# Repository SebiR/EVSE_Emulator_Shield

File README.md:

# EVSE Emulator Arduino Shield
An Arduino shield to emulate an EVSE (Electric Vehicle Supply Equipment), so basically it emulates a car charger

## Features
* on-board charge pump and inverter for +12/-12V pilot signal
* Pilot level and PP level go to ADC channels
* Status LEDs

## Firmware
The Firmware is still in progress. It will be documented once finished

### Known Issues
* ADC values are dependent from USB voltage

## Resources
https://www.goingelectric.de/wiki/Typ2-Signalisierung-und-Steckercodierung/

## Disclaimer
This project was created to test an EV emulator. This project is not intended to be used in an actual Wallbox. 
There are no safety features and neither the firmware nor the hardware are created with robustness and safety in mind.
Although the state machine would be able to work as a full EVSE.

Use at your own risk. Im not liable for burning houses, cars or pants.

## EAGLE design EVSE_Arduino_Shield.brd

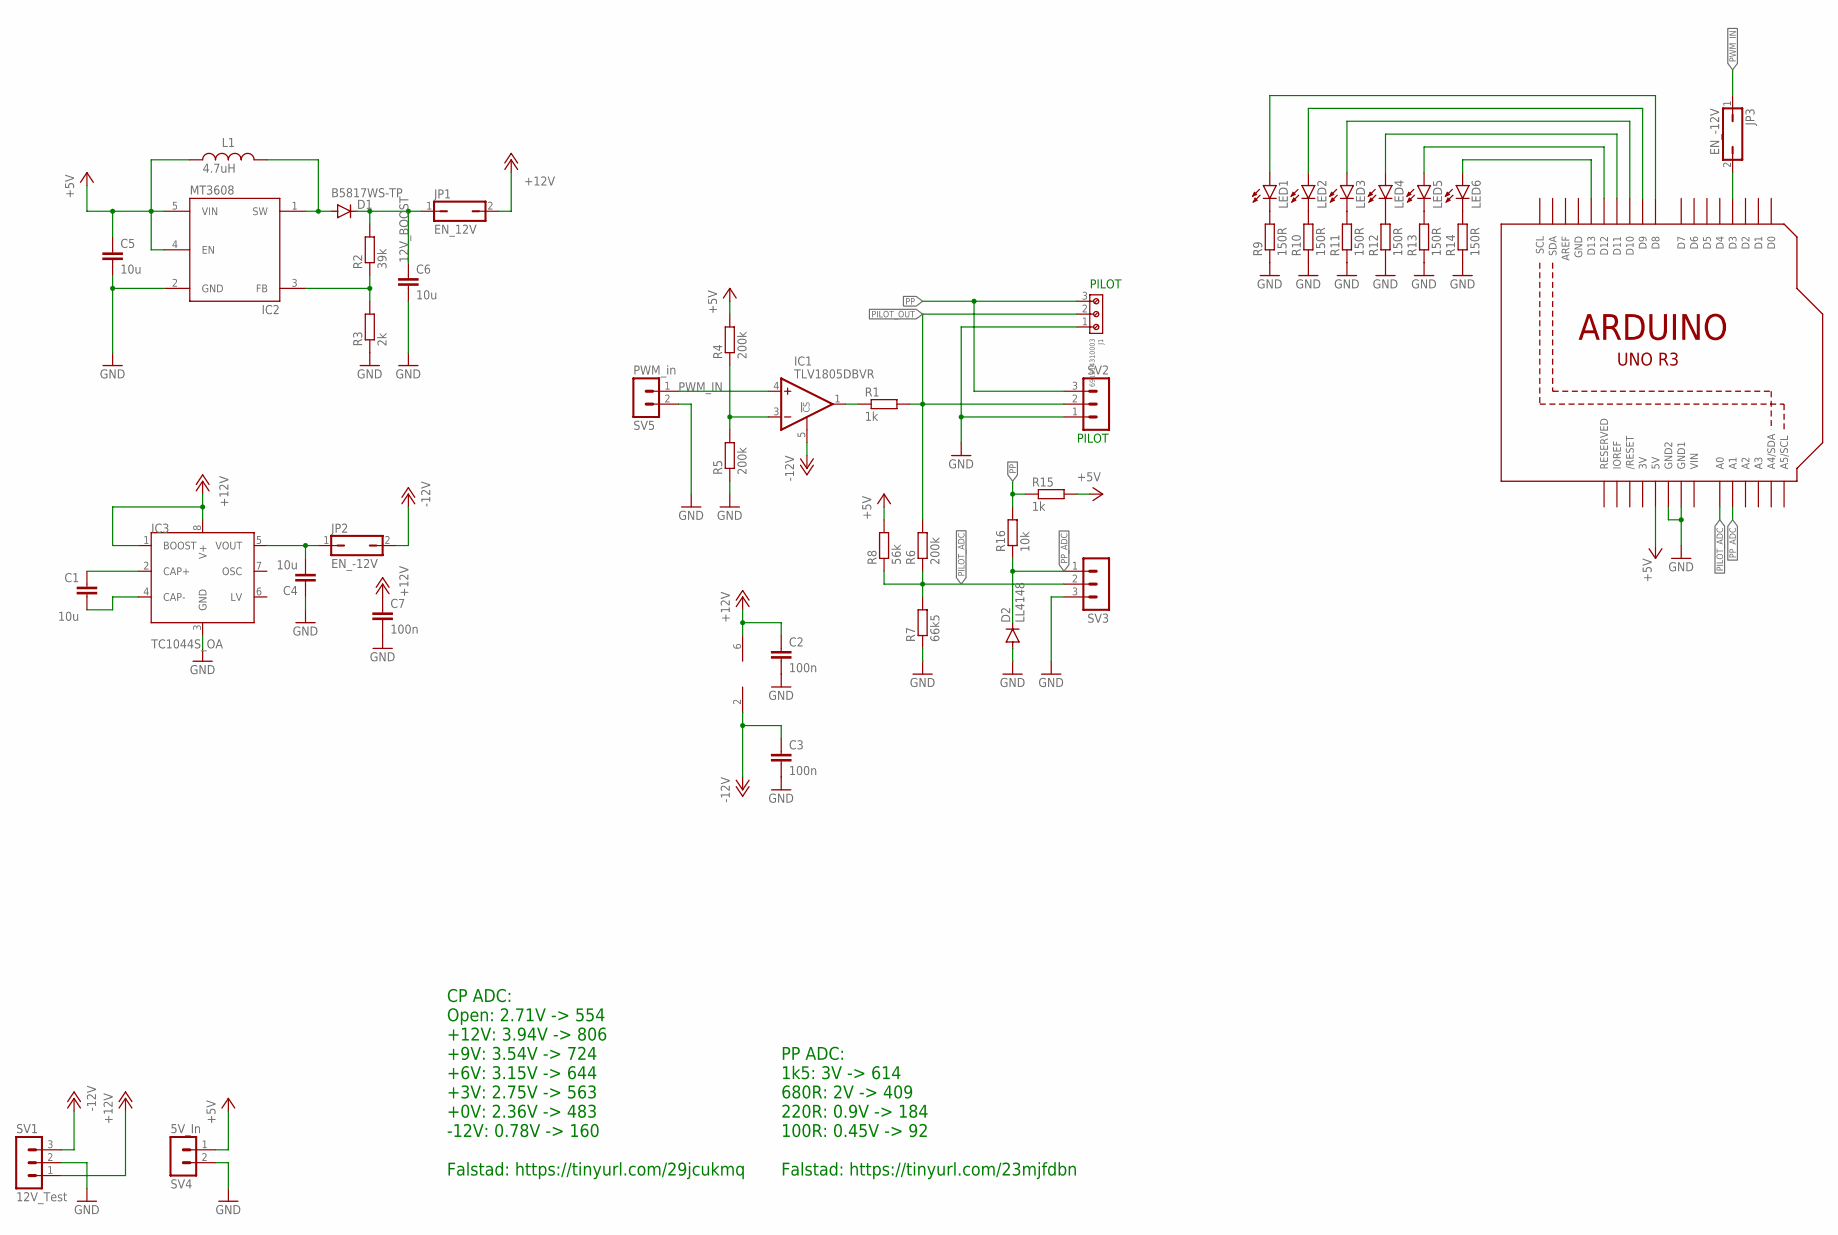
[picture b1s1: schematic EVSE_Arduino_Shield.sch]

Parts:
C1, C4, C5, C6: 10u; C0805
C2, C3, C7: 100n; C0603
D1: B5817WS-TP; SOD323-R
D2: LL4148; SOD80C
IC1: TLV1805DBVR; SOT23-6
IC2: MT3608; SOT23-6
IC3: TC1044S_OA; SO08
J1: 691214310003
JP1: EN_12V; JP1
JP2, JP3: EN_-12V; JP1
L1: 4.7uH; WE-PMI_0805_H1
LED1, LED2, LED3, LED4, LED5, LED6: LEDCHIP-LED0603; CHIP-LED0603
R1: 1k; R0805
R2: 39k; R0603
R3: 2k; R0603
R4, R5, R6: 200k; R0603
R7: 66k5; R0603
R8: 56k; R0603
R9, R10, R11, R12, R13, R14: 150R; R0603
R15: 1k; R0603
R16: 10k; R0603
SV1: 12V_Test; MA03-1
SV2, SV3: MA03-1
SV4: 5V_In; MA02-1
SV5: PWM_in; MA02-1
U2: ARDUINOR3-DIMENSION; ARDUINOR3

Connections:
3V: U2.3V
12V_BOOST: C6.1, D1.C, JP1.1, R2.2
+5V: C5.1, IC2.4 (EN), IC2.5 (VIN), L1.1, R4.2, R8.2, R15.2, SV4.1, U2.5V
+12V: C2.1, C7.1, IC1.6 (V+), IC3.1 (BOOST), IC3.8 (V+), JP1.2, SV1.1
-12V: C3.1, IC1.2 (V-), IC1.5 (!CS), JP2.2, SV1.3
BOOST_SW: D1.A, IC2.1 (SW), L1.2
GND: C2.2, C3.2, C4.1, C5.2, C6.2, C7.2, D2.A, IC2.2 (GND), IC3.3 (GND), J1.1, R3.1, R5.1, R7.1, R9.1, R10.1, R11.1, R12.1, R13.1, R14.1, SV1.2, SV2.1, SV3.3, SV4.2, SV5.2, U2.GND, U2.GND1, U2.GND2
unnamed: LED1.C, R9.2
unnamed: LED2.C, R10.2
unnamed: IC2.3 (FB), R2.1, R3.2
unnamed: IC1.1 (OUT), R1.1
unnamed: JP3.2, U2.D3
unnamed: LED3.C, R11.2
unnamed: C4.2, IC3.5 (VOUT), JP2.1
unnamed: IC1.3 (-IN), R4.1, R5.2
unnamed: LED4.C, R12.2
unnamed: LED5.C, R13.2
unnamed: C1.1, IC3.2 (CAP+)
unnamed: C1.2, IC3.4 (CAP-)
unnamed: LED6.C, R14.2
unnamed: LED6.A, U2.D13
unnamed: LED5.A, U2.D12
unnamed: LED4.A, U2.D11
unnamed: LED3.A, U2.D10
unnamed: LED2.A, U2.D9
unnamed: LED1.A, U2.D8
PILOT_ADC: R6.1, R7.2, R8.1, SV3.2, U2.A0
PILOT_OUT: J1.2, R1.2, R6.2, SV2.2
PP: J1.3, R15.1, R16.2, SV2.3
PP_ADC: D2.C, R16.1, SV3.1, U2.A1
PWM_IN: IC1.4 (+IN), JP3.1, SV5.1
VIN: U2.VIN

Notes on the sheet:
PILOT
CP ADC: Open: 2.71V -> 554 +12V: 3.94V -> 806 +9V: 3.54V -> 724 +6V: 3.15V -> 644 +3V: 2.75V -> 563 +0V: 2.36V -> 483 -12V: 0.78V -> 160 Falstad: https://tinyurl.com/29jcukmq
PP ADC: 1k5: 3V -> 614 680R: 2V -> 409 220R: 0.9V -> 184 100R: 0.45V -> 92 Falstad: https://tinyurl.com/23mjfdbn

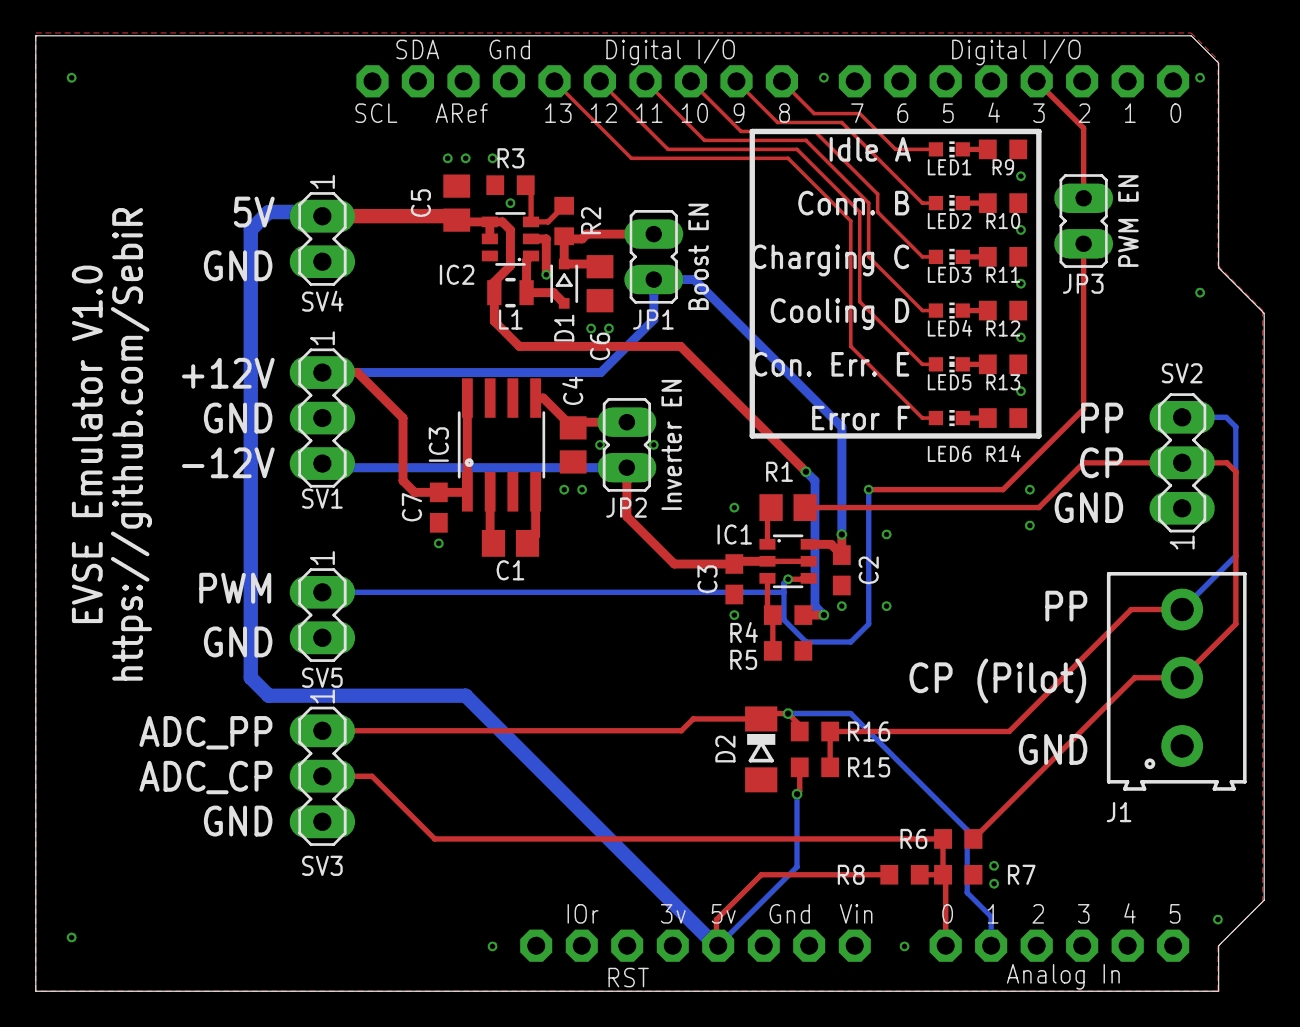
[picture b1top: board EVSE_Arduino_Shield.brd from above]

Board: 2 copper layers, 68.6 x 53.3 mm, 45 parts (0 on the bottom side), 30 nets.

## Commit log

2023-08-18 * Fixed missing values of R2, R3, C5, C1, C6, C4
2023-08-18 * Created new Schematic Output with added component values
2023-08-19 * Added very first stage of firmware (Just a basic LED test. Nothing more)
2023-08-20 * Started abstraction on FW. Still only blinking LEDs.
2023-08-20 Added PWM output control functions and added (empty) interrupt function for ADC measurement when PWM output is on high cycle
2023-08-20 Started FSM (finite state machine) for connection handling
2023-08-20 Started Pilot ADC logic and voltage to STATE conversion
2023-08-21 * Added Pilot ADC function incl. averaging * Added PWM status according to Connection State (fixed 50% for now)
2023-08-24 Started on PP adc functions. Not much yet. Hardware is confirmed to work with minor issues.
2023-08-24 *updated documentation * changed ADC raw values for CP
2023-09-03 * Cleaned Code a bit * Fixed Issue #1 - PWM is now on D3 * Fixed Issue #2 . MT3608 has the correct pin out now * Re-generated GERBER and SCH
2024-07-14 Small Change
2025-06-04 * Updated current output struct to include different max. output currents (no further use yet)

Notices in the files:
parts and their libraries:
Wurth_Power Magnetics_WE-PMI: Copyright: Würth Elektronik
